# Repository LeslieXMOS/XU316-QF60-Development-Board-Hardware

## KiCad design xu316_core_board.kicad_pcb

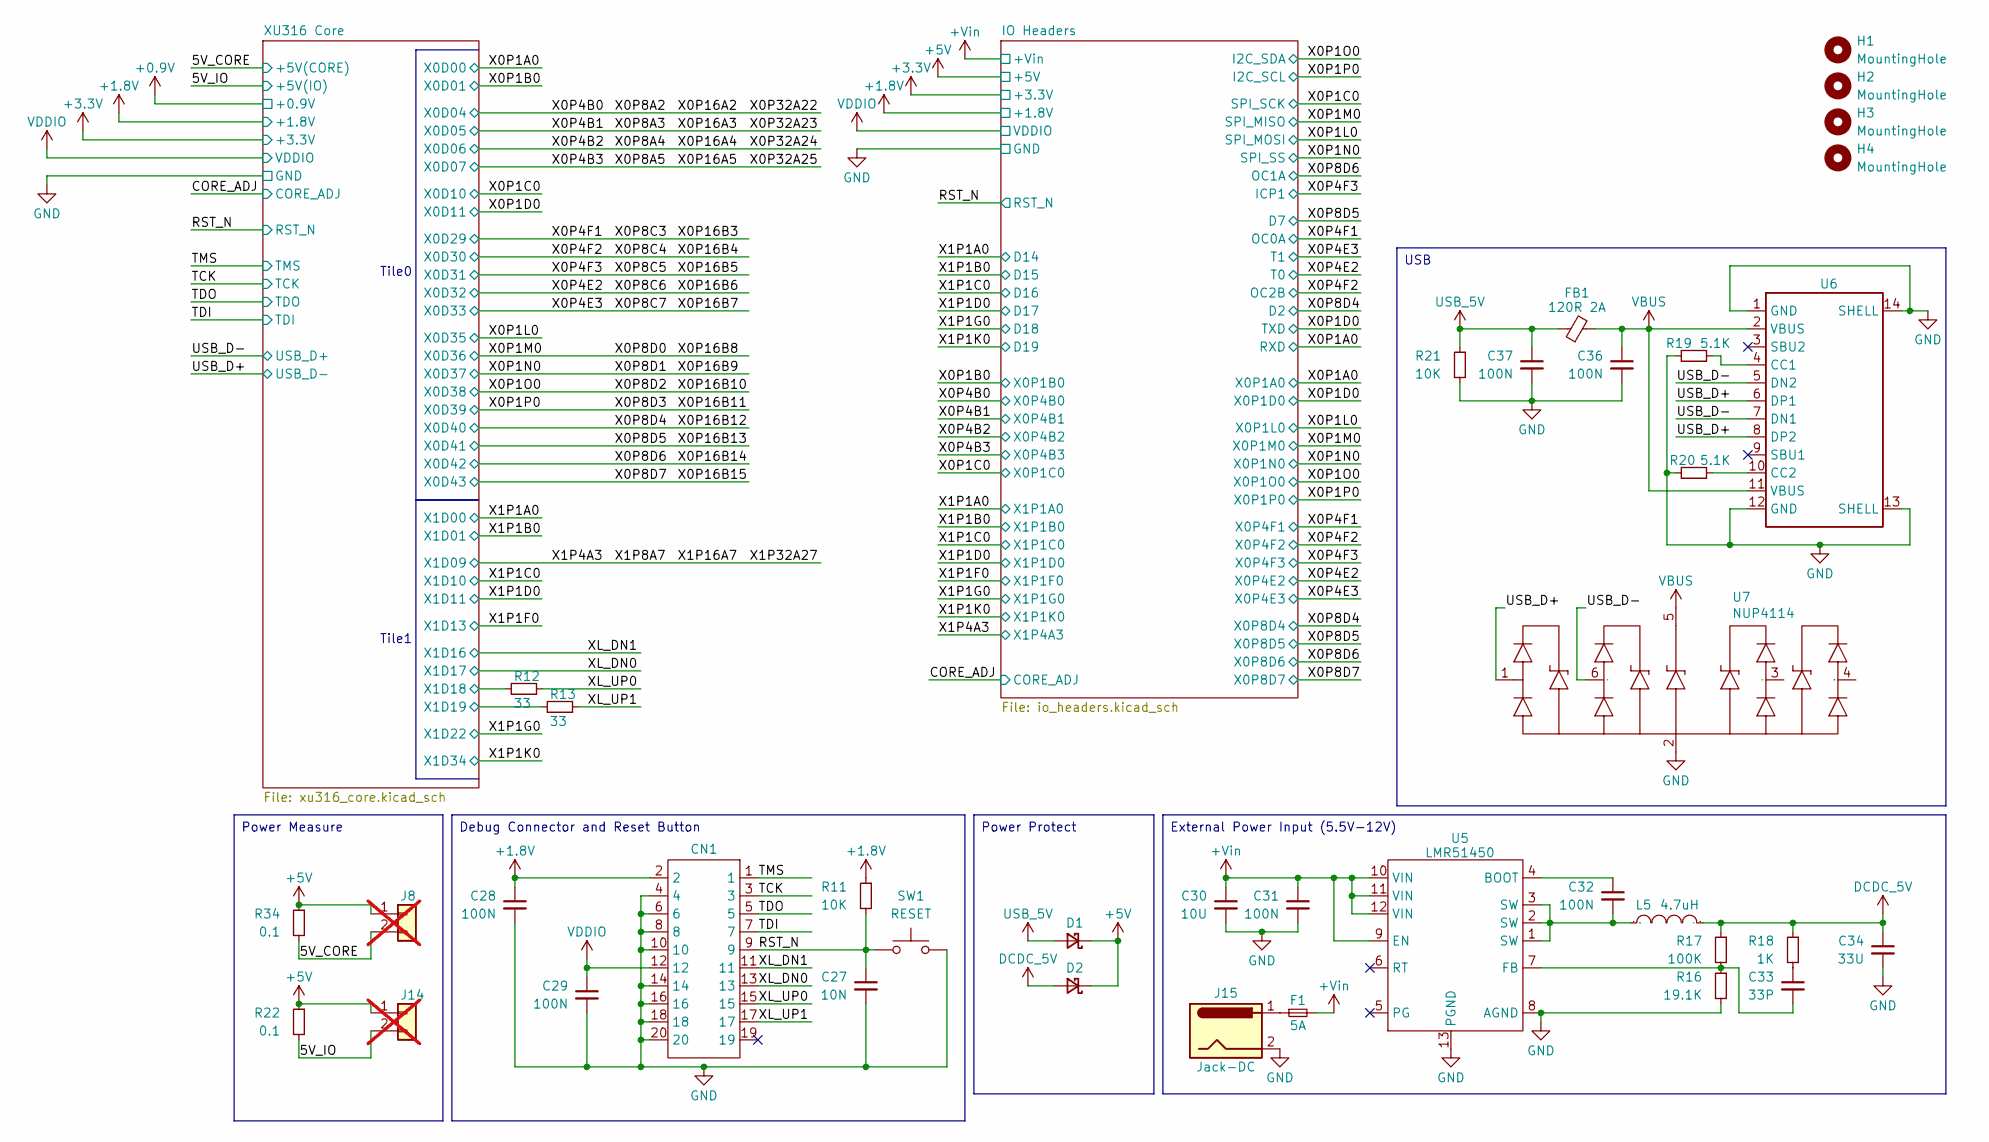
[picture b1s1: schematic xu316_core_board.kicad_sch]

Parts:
C27: 10N; C_0402_1005Metric
C28, C29, C31, C32, C36, C37: 100N; C_0402_1005Metric
C30: 10U; C_1206_3216Metric
C33: 33P; C_0402_1005Metric
C34: 33U; CP_Elec_4x5.4; JLCParts C53200078
CN1: HX JN1.27-2x10P ZZ H4.9; CONN-TH_20P-P1.27_BH127V-20P-H49; Manufacturer Part HX JN1.27-2x10P ZZ H4.9; LCSC Part Name 1.27mm 2x10P 排数:2 每排P数:10
D1, D2: D_Schottky_Small; D_SMA
F1: 5A; Fuse_2512_6332Metric
FB1: 120R 2A; L_0603_1608Metric
H1, H2, H3, H4: MountingHole; MountingHole_3.2mm_M3
J8, J14: Conn_01x02; PinHeader_1x02_P2.54mm_Vertical; not fitted
J15: Jack-DC; BarrelJack_GCT_DCJ200-10-A_Horizontal
L5: 4.7uH; IND-SMD_L7.0-W6.6; Manufacturer Part FXL0630-4R7-M; LCSC Part Name 4.7uH ±20% 9A
R11, R21: 10K; R_0402_1005Metric
R12, R13: 33; R_0402_1005Metric
R16: 19.1K; R_0402_1005Metric
R17: 100K; R_0402_1005Metric
R18: 1K; R_0402_1005Metric
R19, R20: 5.1K; R_0402_1005Metric
R22, R34: 0.1; R_1206_3216Metric; JLCPart C411236
SW1: RESET; SW_Push_1P1T_NO_6x6mm_H9.5mm
U5: LMR51450; WSON-12_L3.0-W3.0-P0.50-TL-EP-2; Manufacturer Part LMR51450FNDRRR; LCSC Part Name 降压型 5A 4V~36V
U6: USB-C-SMD_TYPE-C-6PIN-2MD-073; Manufacturer Part TypeC-16PIN; LCSC Part Name TypeC-16PIN
U7: NUP4114; SC-88-6_L2.0-W1.3-P0.65-LS2.1-BL; Manufacturer Part NUP4114UCLW1T1G; LCSC Part Name NUP4114UCLW1T1G 停产

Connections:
+1.8V: C28.1, CN1.2, R11.1; also elsewhere on the board
+5V: D1.1 (K), D2.1 (K), J8.1, J14.1, R22.1, R34.1; also elsewhere on the board
+5V(CORE): J8.2, R34.2; also elsewhere on the board
+5V(IO): J14.2, R22.2; also elsewhere on the board
+Vin: C30.1, C31.1, F1.2, U5.9 (EN), U5.10 (VIN), U5.11 (VIN), U5.12 (VIN); also elsewhere on the board
/RST_N: C27.1, CN1.9, R11.2, SW1.1; also elsewhere on the board
/TCK: CN1.3; also elsewhere on the board
/TDI: CN1.7; also elsewhere on the board
/TDO: CN1.5; also elsewhere on the board
/TMS: CN1.1; also elsewhere on the board
/USB_D+: U6.6 (DP1), U6.8 (DP2), U7.1; also elsewhere on the board
/USB_D-: U6.5 (DN2), U6.7 (DN1), U7.6; also elsewhere on the board
/XL_DN0: CN1.13; also elsewhere on the board
/XL_DN1: CN1.11; also elsewhere on the board
/XL_UP0: CN1.15, R12.1
/XL_UP1: CN1.17, R13.1
/XU316 Core/X1D18: R12.2; also elsewhere on the board
/XU316 Core/X1D19: R13.2; also elsewhere on the board
DCDC_5V: C34.1, D2.2 (A), L5.2, R17.1, R18.1
GND: C27.2, C28.2, C29.2, C30.2, C31.2, C34.2, C36.2, C37.2, CN1.4, CN1.6, CN1.8, CN1.10, CN1.14, CN1.16, CN1.18, CN1.20, J15.2, R16.2, R19.2, R20.2, R21.2, SW1.2, U5.8 (AGND), U5.13 (PGND), U6.1 (GND), U6.12 (GND), U6.13 (SHELL), U6.14 (SHELL), U7.2; also elsewhere on the board
unnamed: C32.2, L5.1, U5.1 (SW), U5.2 (SW), U5.3 (SW)
unnamed: C33.1, R18.2
unnamed: F1.1, J15.1
unnamed: C32.1, U5.4 (BOOT)
unnamed: C33.2, R16.1, R17.2, U5.7 (FB)
unnamed: R19.1, U6.4 (CC1)
unnamed: R20.1, U6.10 (CC2)
USB_5V: C37.1, D1.2 (A), FB1.1, R21.1
VBUS: C36.1, FB1.2, U6.2 (VBUS), U6.11 (VBUS), U7.5
VDDIO: C29.1, CN1.12; also elsewhere on the board

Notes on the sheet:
Tile0
Tile1
Debug Connector and Reset Button
Power Protect
External Power Input (5.5V-12V)
USB
Power Measure

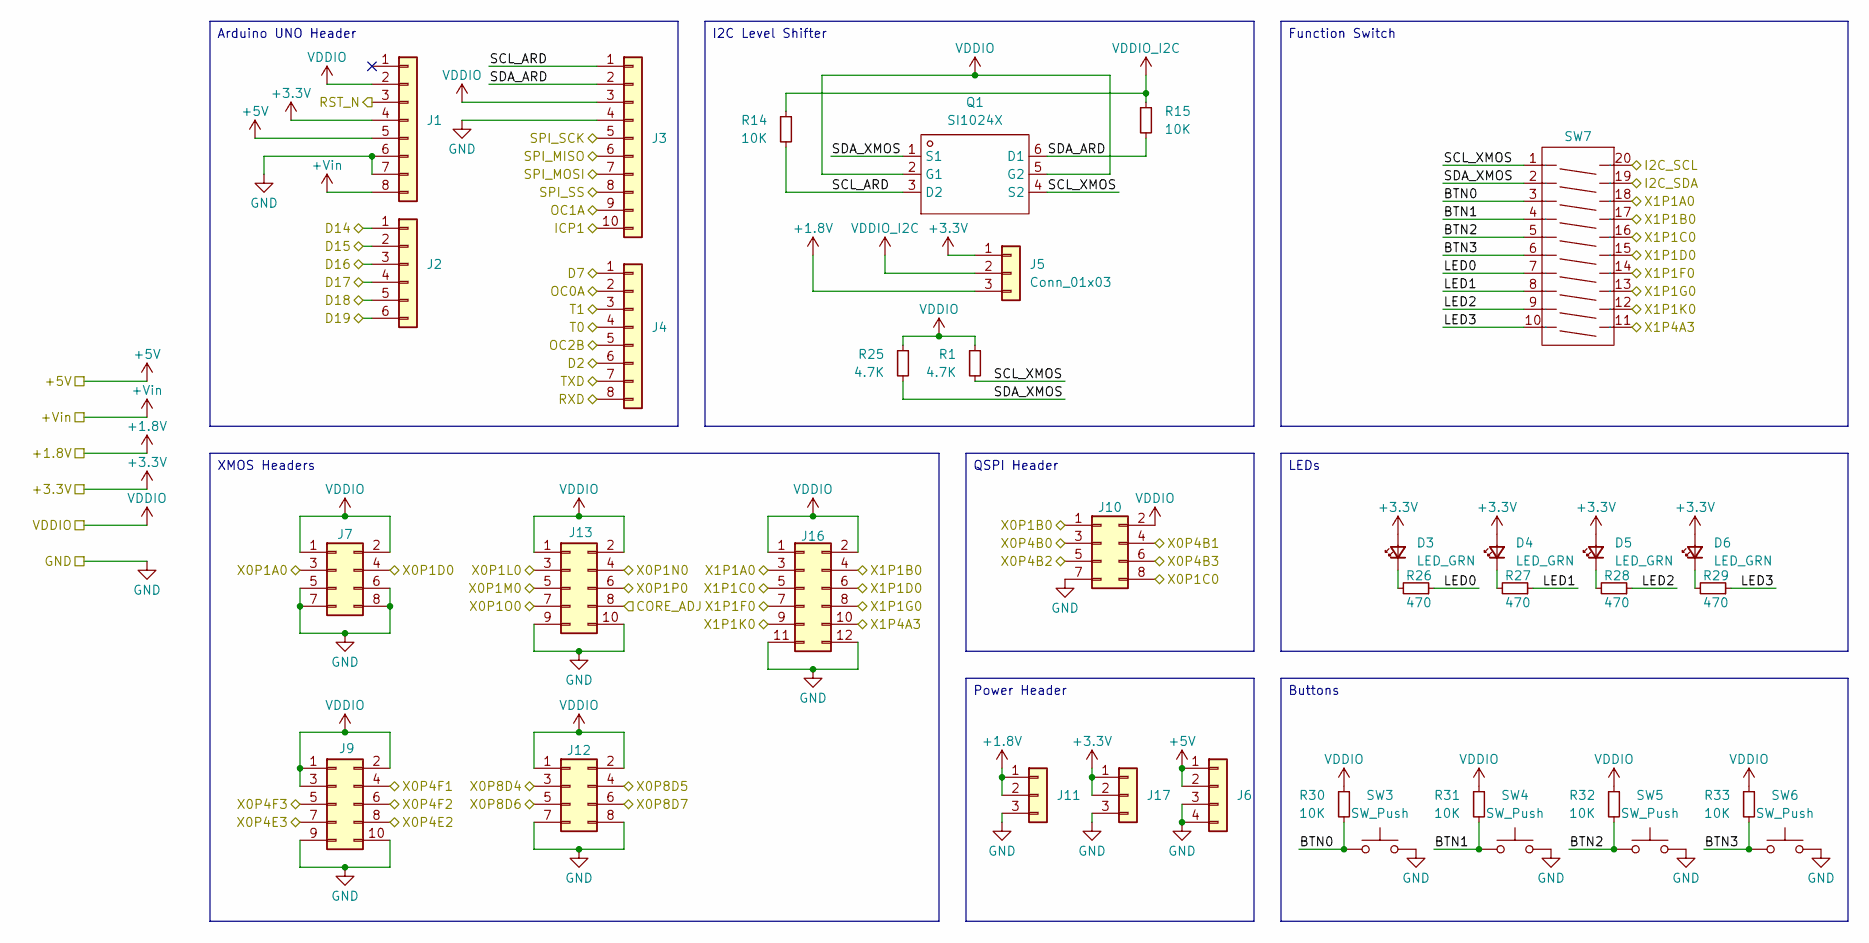
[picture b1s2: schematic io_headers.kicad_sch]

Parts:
D3, D4, D5, D6: LED_GRN; LED_0805_2012Metric
J1, J4: Conn_01x08; PinHeader_1x08_P2.54mm_Vertical
J2: Conn_01x06; PinHeader_1x06_P2.54mm_Vertical
J3: Conn_01x10; PinHeader_1x10_P2.54mm_Vertical
J5, J11, J17: Conn_01x03; PinHeader_1x03_P2.54mm_Vertical
J6: Conn_01x04; PinHeader_1x04_P2.54mm_Vertical
J7, J10, J12: Conn_02x04_Odd_Even; PinHeader_2x04_P2.54mm_Vertical
J9, J13: Conn_02x05_Odd_Even; PinHeader_2x05_P2.54mm_Vertical
J16: Conn_02x06_Odd_Even; PinHeader_2x06_P2.54mm_Vertical
Q1: SI1024X; SOT-563_L1.6-W1.2-P0.50-LS1.6-BL; Manufacturer Part SI1024X-T1-GE3; LCSC Part Name 2个N沟道 耐压:20V 电流:600mA
R1, R25: 4.7K; R_0402_1005Metric
R14, R15, R30, R31, R32, R33: 10K; R_0402_1005Metric
R26, R27, R28, R29: 470; R_0402_1005Metric
SW3, SW4, SW5, SW6: SW_Push; SW_Push_1P1T_NO_6x6mm_H9.5mm
SW7: SW-SMD_20P-L14.3-W5.4-P1.27-LS8.3; Manufacturer Part DS-10P; LCSC Part Name 1.27mm间距10位 贴片黑色S脚 拨码开关

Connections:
+1.8V: J5.3, J11.1, J11.2; also elsewhere on the board
+3.3V: D3.2 (A), D4.2 (A), D5.2 (A), D6.2 (A), J1.4, J5.1, J17.1, J17.2; also elsewhere on the board
+5V: J1.5, J6.1, J6.2; also elsewhere on the board
+Vin: J1.8; also elsewhere on the board
/CORE_ADJ: J13.8; also elsewhere on the board
/IO Headers/BTN0: R30.2, SW3.1, SW7.3
/IO Headers/BTN1: R31.2, SW4.1, SW7.4
/IO Headers/BTN2: R32.2, SW5.1, SW7.5
/IO Headers/BTN3: R33.2, SW6.1, SW7.6
/IO Headers/LED0: R26.1, SW7.7
/IO Headers/LED1: R27.1, SW7.8
/IO Headers/LED2: R28.1, SW7.9
/IO Headers/LED3: R29.1, SW7.10
/IO Headers/SCL_ARD: J3.1, Q1.3 (D2), R14.2
/IO Headers/SCL_XMOS: Q1.4 (S2), R1.2, SW7.1
/IO Headers/SDA_ARD: J3.2, Q1.6 (D1), R15.2
/IO Headers/SDA_XMOS: Q1.1 (S1), R25.2, SW7.2
/RST_N: J1.3; also elsewhere on the board
/X0P1A0: J4.8, J7.3; also elsewhere on the board
/X0P1B0: J10.1; also elsewhere on the board
/X0P1C0: J3.5, J10.8; also elsewhere on the board
/X0P1D0: J4.7, J7.4; also elsewhere on the board
/X0P1L0: J3.7, J13.3; also elsewhere on the board
/X0P16A2: J10.3; also elsewhere on the board
/X0P16A3: J10.4; also elsewhere on the board
/X0P16A4: J10.5; also elsewhere on the board
/X0P16A5: J10.6; also elsewhere on the board
/X0P16B3: J4.2, J9.4; also elsewhere on the board
/X0P16B4: J4.5, J9.6; also elsewhere on the board
/X0P16B5: J3.10, J9.5; also elsewhere on the board
/X0P16B6: J4.4, J9.8; also elsewhere on the board
/X0P16B7: J4.3, J9.7; also elsewhere on the board
/X0P16B8: J3.6, J13.5; also elsewhere on the board
/X0P16B9: J3.8, J13.4; also elsewhere on the board
/X0P16B10: J13.7, SW7.19; also elsewhere on the board
/X0P16B11: J13.6, SW7.20; also elsewhere on the board
/X0P16B12: J4.6, J12.3; also elsewhere on the board
/X0P16B13: J4.1, J12.4; also elsewhere on the board
/X0P16B14: J3.9, J12.5; also elsewhere on the board
/X0P16B15: J12.6; also elsewhere on the board
/X1P1A0: J2.1, J16.3, SW7.18; also elsewhere on the board
/X1P1B0: J2.2, J16.4, SW7.17; also elsewhere on the board
/X1P1C0: J2.3, J16.5, SW7.16; also elsewhere on the board
/X1P1D0: J2.4, J16.6, SW7.15; also elsewhere on the board
/X1P1F0: J16.7, SW7.14; also elsewhere on the board
/X1P1G0: J2.5, J16.8, SW7.13; also elsewhere on the board
/X1P1K0: J2.6, J16.9, SW7.12; also elsewhere on the board
/X1P16A7: J16.10, SW7.11; also elsewhere on the board
GND: J1.6, J1.7, J3.4, J6.3, J6.4, J7.5, J7.6, J7.7, J7.8, J9.9, J9.10, J10.7, J11.3, J12.7, J12.8, J13.9, J13.10, J16.11, J16.12, J17.3, SW3.2, SW4.2, SW5.2, SW6.2; also elsewhere on the board
unnamed: D3.1 (K), R26.2
unnamed: D4.1 (K), R27.2
unnamed: D5.1 (K), R28.2
unnamed: D6.1 (K), R29.2
VDDIO: J1.2, J3.3, J7.1, J7.2, J9.1, J9.2, J9.3, J10.2, J12.1, J12.2, J13.1, J13.2, J16.1, J16.2, Q1.2 (G1), Q1.5 (G2), R1.1, R25.1, R30.1, R31.1, R32.1, R33.1; also elsewhere on the board
VDDIO_I2C: J5.2, R14.1, R15.1

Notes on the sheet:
Function Switch
I2C Level Shifter
XMOS Headers
QSPI Header
LEDs
Arduino UNO Header
Power Header
Buttons

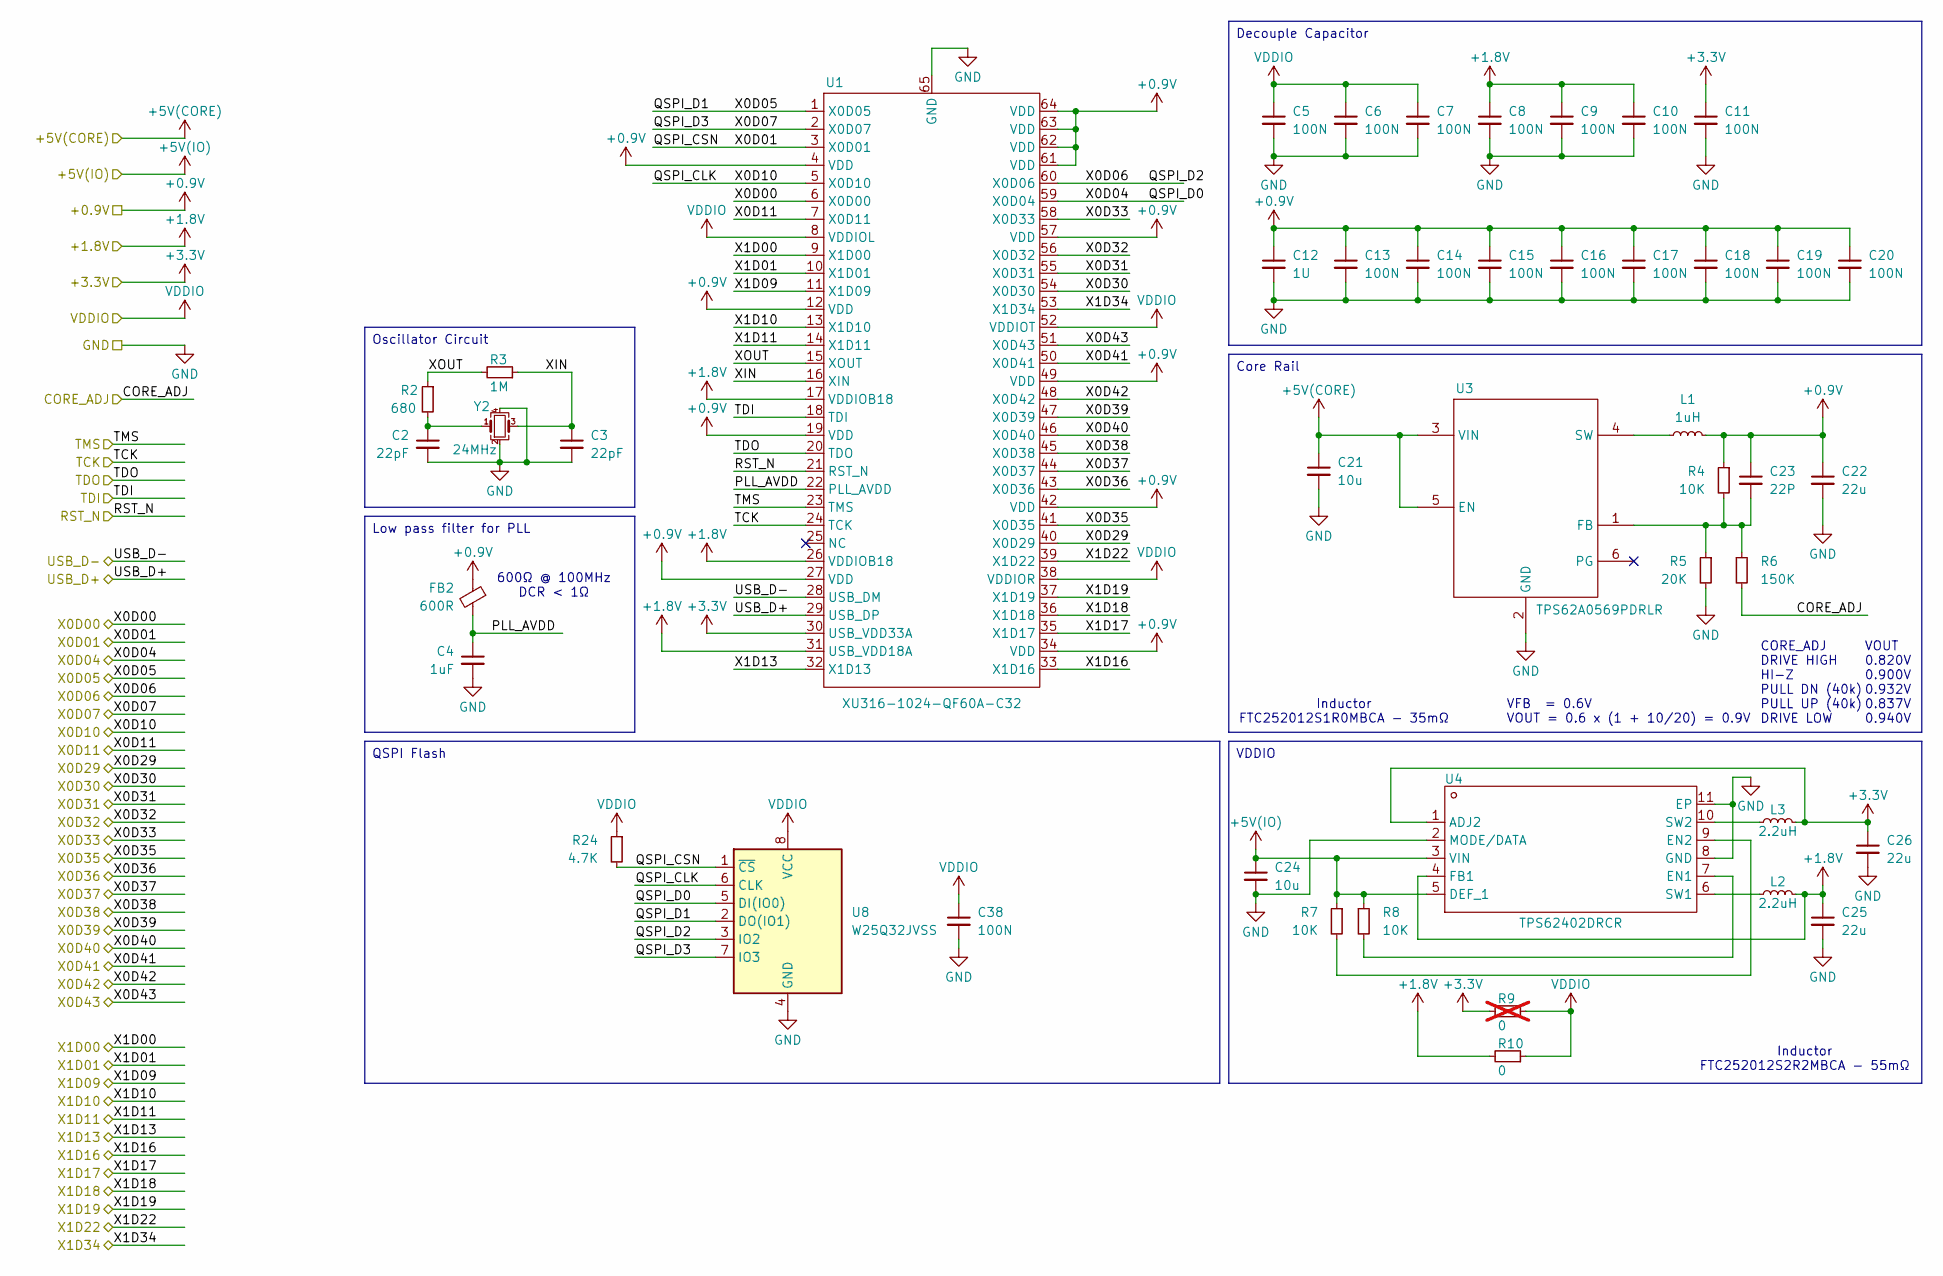
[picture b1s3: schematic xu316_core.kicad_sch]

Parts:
C2, C3: 22pF; C_0402_1005Metric
C4: 1uF; C_0402_1005Metric
C5, C6, C7, C8, C9, C10, C11, C13, C14, C15, C16, C17, C18, C19, C20, C38: 100N; C_0402_1005Metric
C12: 1U; C_0402_1005Metric
C21, C24: 10u; C_0603_1608Metric
C22, C25, C26: 22u; C_0402_1005Metric
C23: 22P; C_0402_1005Metric
FB2: 600R; L_0402_1005Metric
L1: 1uH; L_1008_2520Metric
L2, L3: 2.2uH; L_1008_2520Metric
R2: 680; R_0402_1005Metric
R3: 1M; R_0402_1005Metric
R4, R7, R8: 10K; R_0402_1005Metric
R5: 20K; R_0402_1005Metric
R6: 150K; R_0402_1005Metric
R9: 0; R_0805_2012Metric; not fitted
R10: 0; R_0805_2012Metric
R24: 4.7K; R_0402_1005Metric
U1: XU316-1024-QF60A-C32; QFN-60_L7.0-W7.0-P0.40-TL-EP_XU316-1024; Manufacturer Part XU316-1024-QF60A-C32; LCSC Part Name XU316-1024-QF60A-C32
U3: TPS62A0569PDRLR; sot-563-6
U4: TPS62402DRCR; VSON-10_L3.0-W3.0-P0.50-BL-EP_TPS62410DRCR; Manufacturer Part TPS62402DRCR; LCSC Part Name 降压型 400mA 2.5V~6V
U8: W25Q32JVSS; SOIC-8_5.23x5.23mm_P1.27mm
Y2: 24MHz; Crystal_SMD_2016-4Pin_2.0x1.6mm; part XTM20024000JT00351001

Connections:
+0.9V: C12.1, C13.1, C14.1, C15.1, C16.1, C17.1, C18.1, C19.1, C20.1, C22.1, C23.1, FB2.1, L1.2, R4.1, U1.4 (VDD), U1.12 (VDD), U1.19 (VDD), U1.27 (VDD), U1.34 (VDD), U1.42 (VDD), U1.49 (VDD), U1.57 (VDD), U1.61 (VDD), U1.62 (VDD), U1.63 (VDD), U1.64 (VDD)
+1.8V: C8.1, C9.1, C10.1, C25.1, L2.2, R10.2, U1.17 (VDDIOB18), U1.26 (VDDIOB18), U1.31 (USB_VDD18A), U4.4 (FB1); also elsewhere on the board
+3.3V: C11.1, C26.1, L3.2, R9.2, U1.30 (USB_VDD33A), U4.1 (ADJ2); also elsewhere on the board
+5V(CORE): C21.1, U3.3 (VIN), U3.5 (EN); also elsewhere on the board
+5V(IO): C24.1, R7.1, R8.1, U4.3 (VIN), U4.5 (DEF_1); also elsewhere on the board
/CORE_ADJ: R6.2; also elsewhere on the board
/RST_N: U1.21 (RST_N); also elsewhere on the board
/TCK: U1.24 (TCK); also elsewhere on the board
/TDI: U1.18 (TDI); also elsewhere on the board
/TDO: U1.20 (TDO); also elsewhere on the board
/TMS: U1.23 (TMS); also elsewhere on the board
/USB_D+: U1.28 (USB_DM); also elsewhere on the board
/USB_D-: U1.29 (USB_DP); also elsewhere on the board
/X0P1A0: U1.6 (X0D00); also elsewhere on the board
/X0P1B0: R24.2, U1.3 (X0D01), U8.1 (~CS); also elsewhere on the board
/X0P1C0: U1.5 (X0D10), U8.6 (CLK); also elsewhere on the board
/X0P1D0: U1.7 (X0D11); also elsewhere on the board
/X0P1L0: U1.41 (X0D35); also elsewhere on the board
/X0P16A2: U1.59 (X0D04), U8.5 (DI(IO0)); also elsewhere on the board
/X0P16A3: U1.1 (X0D05), U8.2 (DO(IO1)); also elsewhere on the board
/X0P16A4: U1.60 (X0D06), U8.3 (IO2); also elsewhere on the board
/X0P16A5: U1.2 (X0D07), U8.7 (IO3); also elsewhere on the board
/X0P16B3: U1.40 (X0D29); also elsewhere on the board
/X0P16B4: U1.54 (X0D30); also elsewhere on the board
/X0P16B5: U1.55 (X0D31); also elsewhere on the board
/X0P16B6: U1.56 (X0D32); also elsewhere on the board
/X0P16B7: U1.58 (X0D33); also elsewhere on the board
/X0P16B8: U1.43 (X0D36); also elsewhere on the board
/X0P16B9: U1.44 (X0D37); also elsewhere on the board
/X0P16B10: U1.45 (X0D38); also elsewhere on the board
/X0P16B11: U1.47 (X0D39); also elsewhere on the board
/X0P16B12: U1.46 (X0D40); also elsewhere on the board
/X0P16B13: U1.50 (X0D41); also elsewhere on the board
/X0P16B14: U1.48 (X0D42); also elsewhere on the board
/X0P16B15: U1.51 (X0D43); also elsewhere on the board
/X1P1A0: U1.9 (X1D00); also elsewhere on the board
/X1P1B0: U1.10 (X1D01); also elsewhere on the board
/X1P1C0: U1.13 (X1D10); also elsewhere on the board
/X1P1D0: U1.14 (X1D11); also elsewhere on the board
/X1P1F0: U1.32 (X1D13); also elsewhere on the board
/X1P1G0: U1.39 (X1D22); also elsewhere on the board
/X1P1K0: U1.53 (X1D34); also elsewhere on the board
/X1P16A7: U1.11 (X1D09); also elsewhere on the board
/XL_DN0: U1.35 (X1D17); also elsewhere on the board
/XL_DN1: U1.33 (X1D16); also elsewhere on the board
/XU316 Core/PLL_AVDD: C4.1, FB2.2, U1.22 (PLL_AVDD)
/XU316 Core/X1D18: U1.36 (X1D18); also elsewhere on the board
/XU316 Core/X1D19: U1.37 (X1D19); also elsewhere on the board
/XU316 Core/XIN: C3.1, R3.1, U1.16 (XIN), Y2.3
/XU316 Core/XOUT: R2.1, R3.2, U1.15 (XOUT)
GND: C2.2, C3.2, C4.2, C5.2, C6.2, C7.2, C8.2, C9.2, C10.2, C11.2, C12.2, C13.2, C14.2, C15.2, C16.2, C17.2, C18.2, C19.2, C20.2, C21.2, C22.2, C24.2, C25.2, C26.2, C38.2, R5.2, U1.65 (GND), U3.2 (GND), U4.2 (MODE/DATA), U4.8 (GND), U4.11 (EP), U8.4 (GND), Y2.2, Y2.4; also elsewhere on the board
unnamed: C2.1, R2.2, Y2.1
unnamed: C23.2, R4.2, R5.1, R6.1, U3.1 (FB)
unnamed: L1.1, U3.4 (SW)
unnamed: R8.2, U4.7 (EN1)
unnamed: R7.2, U4.9 (EN2)
unnamed: L2.1, U4.6 (SW1)
unnamed: L3.1, U4.10 (SW2)
VDDIO: C5.1, C6.1, C7.1, C38.1, R9.1, R10.1, R24.1, U1.8 (VDDIOL), U1.38 (VDDIOR), U1.52 (VDDIOT), U8.8 (VCC); also elsewhere on the board

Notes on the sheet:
CORE_ADJ DRIVE HIGH HI-Z PULL DN (40k) PULL UP (40k) DRIVE LOW
Inductor FTC252012S1R0MBCA - 35mΩ
VOUT 0.820V 0.900V 0.932V 0.837V 0.940V
Inductor FTC252012S2R2MBCA - 55mΩ
600Ω @ 100MHz DCR < 1Ω
VFB = 0.6V VOUT = 0.6 x (1 + 10/20) = 0.9V
Core Rail
Decouple Capacitor
Low pass filter for PLL
VDDIO
QSPI Flash
Oscillator Circuit

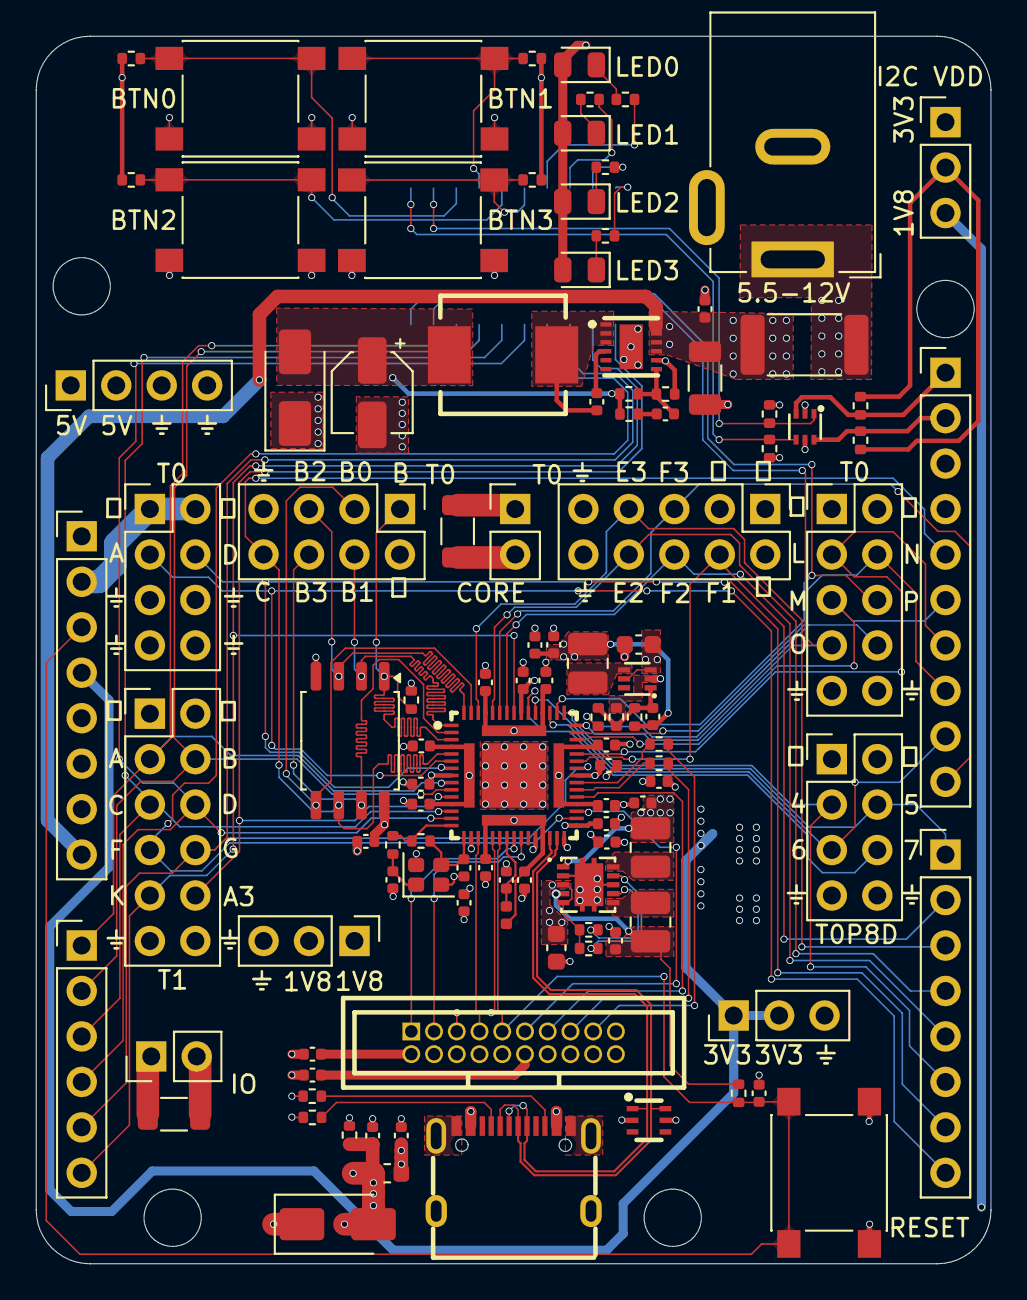
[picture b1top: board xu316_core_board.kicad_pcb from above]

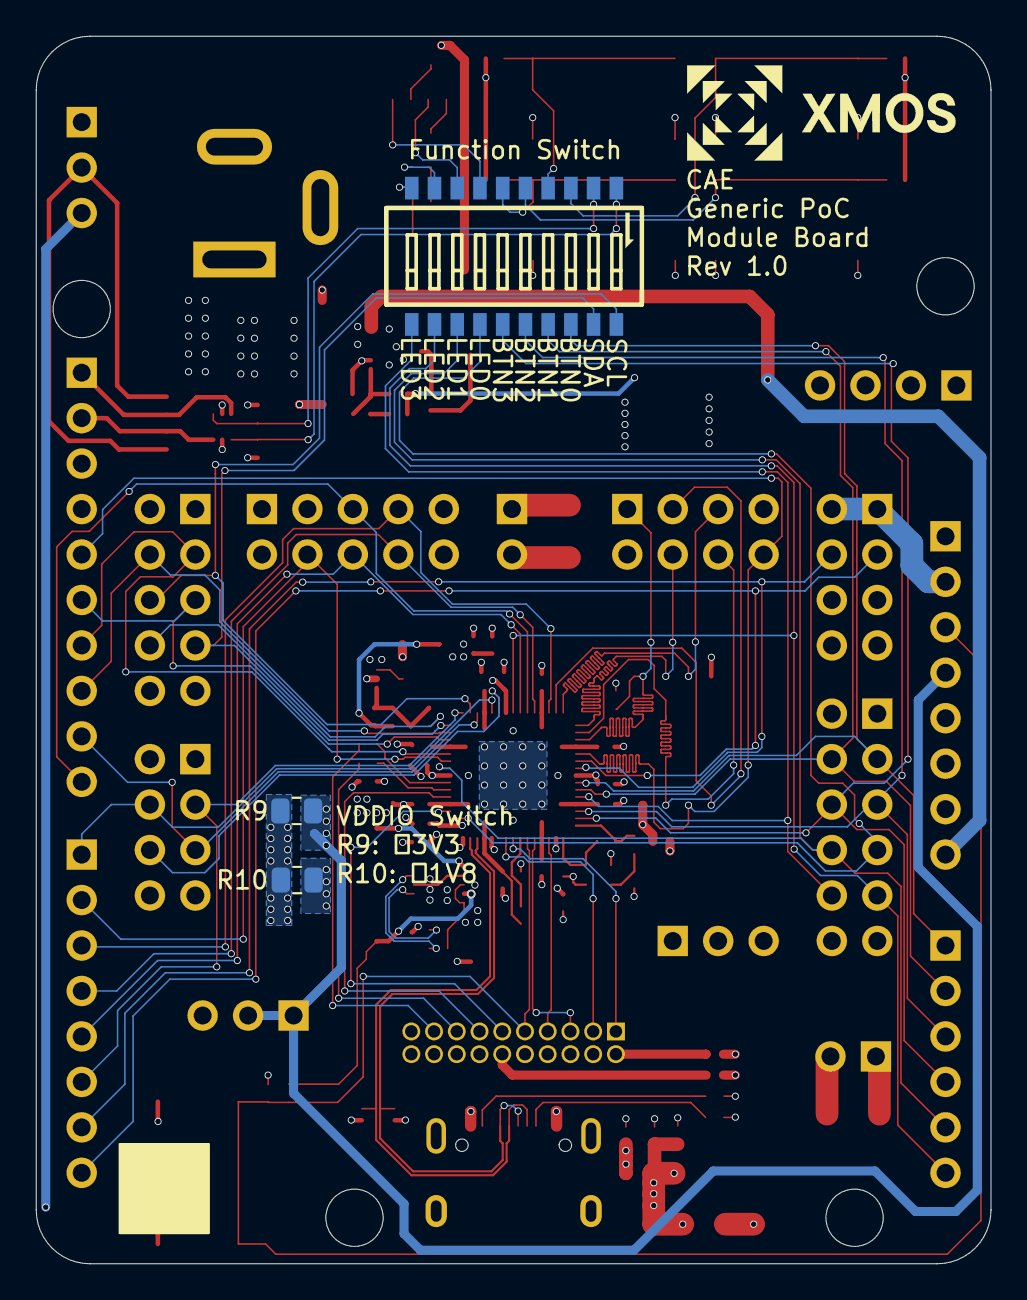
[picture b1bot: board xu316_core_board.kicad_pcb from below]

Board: 4 copper layers, 53.3 x 68.6 mm, 119 parts (3 on the bottom side), 90 nets.
